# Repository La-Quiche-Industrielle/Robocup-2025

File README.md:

# Robocup-2025

## What is Robocup?
[Robocup Junior Soccer Open](https://junior.robocup.org/soccer/) is a league of the international robotic competition: [RoboCup](https://robocup.org).
For this competition, we need to create _two fully autonomous robots_ that play _soccer_ against other teams. We have to design, build and program the robots without external help. This is a really challenging problem because the robots need to be fully autonomous. They need to detect the ball and try to go towards it to hopefully push it towards the goal. A camera system is needed to try to detect the ball based on its color (it's an orange golf ball) and to detect the opponent's goal.

[Learn more about the competition](https://robocup-junior.github.io/soccer-rules/master/rules.html)

## The robots

The robots were built with individual components we found online, that we meshed together using communication protocols such as uart. The frames were 3d printed, and the cone was manufactured with CNC machining.

[More on the components we used](./components.md)

While we prepared for the competition, the robots could reliably place goals and were rather fast:

### What worked
The robots could reliably
- Find the ball
- Go towards the ball and place themselves in positions in which they could start moving towards the goal
- Shoot the ball / place a goal
- Avoid going out of bounds by staying a certain distance from walls
- Recenter when they couldn't see the ball. The robots could always see the ball from the center of the field (except if another robot was hiding it), so a centering function was enough to find the ball if it wasn't in the robot's field of visioin

### What failed
The robots broke in many ways during the national competition which meant we couldn't play for many of the matches:
- The wheels got disconnected from the motor's axies many times, which meant the whole robot became unable to play.
- Many of our N20 motors broke, which meant we didn't even have enough motors for both robots at the end of the competition
- An esp32 broke during the competition, and one of our replacement microcontrollers also failed when we opened the package.
- One of the batteries had a short circuit. Thankfully, the BMS (battery management system) protected the batteries from the short circuit. 

### How we'll fix these issues
- We created a simple 3d printed junction between the motors' axies and the wheels. This worked very well initially, but we hadn't taken the plastic's wear into account nearly enough. For next year, we'll only use metal components on important structural parts such as this.
- Last year, we chose N20 motors because of their low cost and good reviews. During the competitions, we often went above their torque limit, thus hurting the gears and breaking the motors. The N20 motors' torque is around 1kg.cm, and we realised that this wasn't nearly enough for what we wanted our robots to do. Next year, we'll invest in some better motors given sufficient funding, and hard code the torque limit into the program to slow the robots down before they could reach the torque limit and hurt the components.
- We bought many of our components on Aliexpress to reduce costs. Esp32s from aliexpress were within our price range, so we used these microcontrollers. For next year, we'll probably use better and faster microcontrollers such as a [teensy](https://www.sparkfun.com/development-boards/microcontrollers/teensy.html) and from better suppliers if we have the budget to do so.
- The battery had a short circuit because the wiring had become very difficult to work with. We had several dozens of wires going through the robot, and a positive and negative wire must have touched causing the short. This year, we tried designing a pcb, but it had a short circuit. Next year, we'll design a better pcb for the whole robot and try to find more data on pcb design before sending the design to a manufacturer.

### What we learned from our mistakes

___We can't expect the robots not to break:___
This year was a rather frustrating experience as we had worked very hard to create fast and functional robots only to see them fail miserably the day of the competition. We managed to have the robots place goals and avoid going out of bounds, and search for the ball if it couldn't see it and many other challenging actions only to see most components on the robots fail. We had spent hours programming the robots and making them move around on the field, and yet the numerous issues only arised the day of the competition. What we have learned from this is that we need to stress test our robots a lot more. We can no longer expect something to work only because it has worked in the past. Next year, we will push the robots to their limits. We will make them move until something breaks then rebuild that part with a lot more redundancy. We will also source better components given te ressources, and try to build redundancy into each and every part of the robot. We have learned that ___we can't expect that the robot won't break.___, but we need redundant systems to make sure that the system continues to work even if the primary system fails.

### License
This project is licensed under the Mozilla Public License 2.0 - see the [LICENSE](LICENSE) file for details.
## Our Website
Find out more about the team at laquicheindustrielle.com.

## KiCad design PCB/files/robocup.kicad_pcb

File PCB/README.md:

# Custom PCB Design

This is a 2-layer custom PCB designed in **KiCad 9** and manufactured via **JLCPCB**.

---

## About
  
the **PCB** was created using **KiCad 9**, with a focus on simplicity, and ease of assembly.

---

## Specs

-  **Layers**: 2
-  **EDA Tool**: KiCad 9
-  **Manufacturer**: JLCPCB
-  **Board Dimensions**: _[175mm x 175mm]_
-  **Ground pour for thermal management and EMI reduction.**

---

## 📁 Design Files

The following files are included in this repo:

- `*.kicad_pro` – KiCad 9 project file  
- `*.kicad_pcb` – PCB layout  
- `*.sch` – Schematic  
- `*.pdf` – Schematic2  

---

##  Manufacturing

These files were exported for and tested with **JLCPCB**.

- Designed using [KiCad](https://kicad.org/)
- Manufactured by [JLCPCB](https://jlcpcb.com)

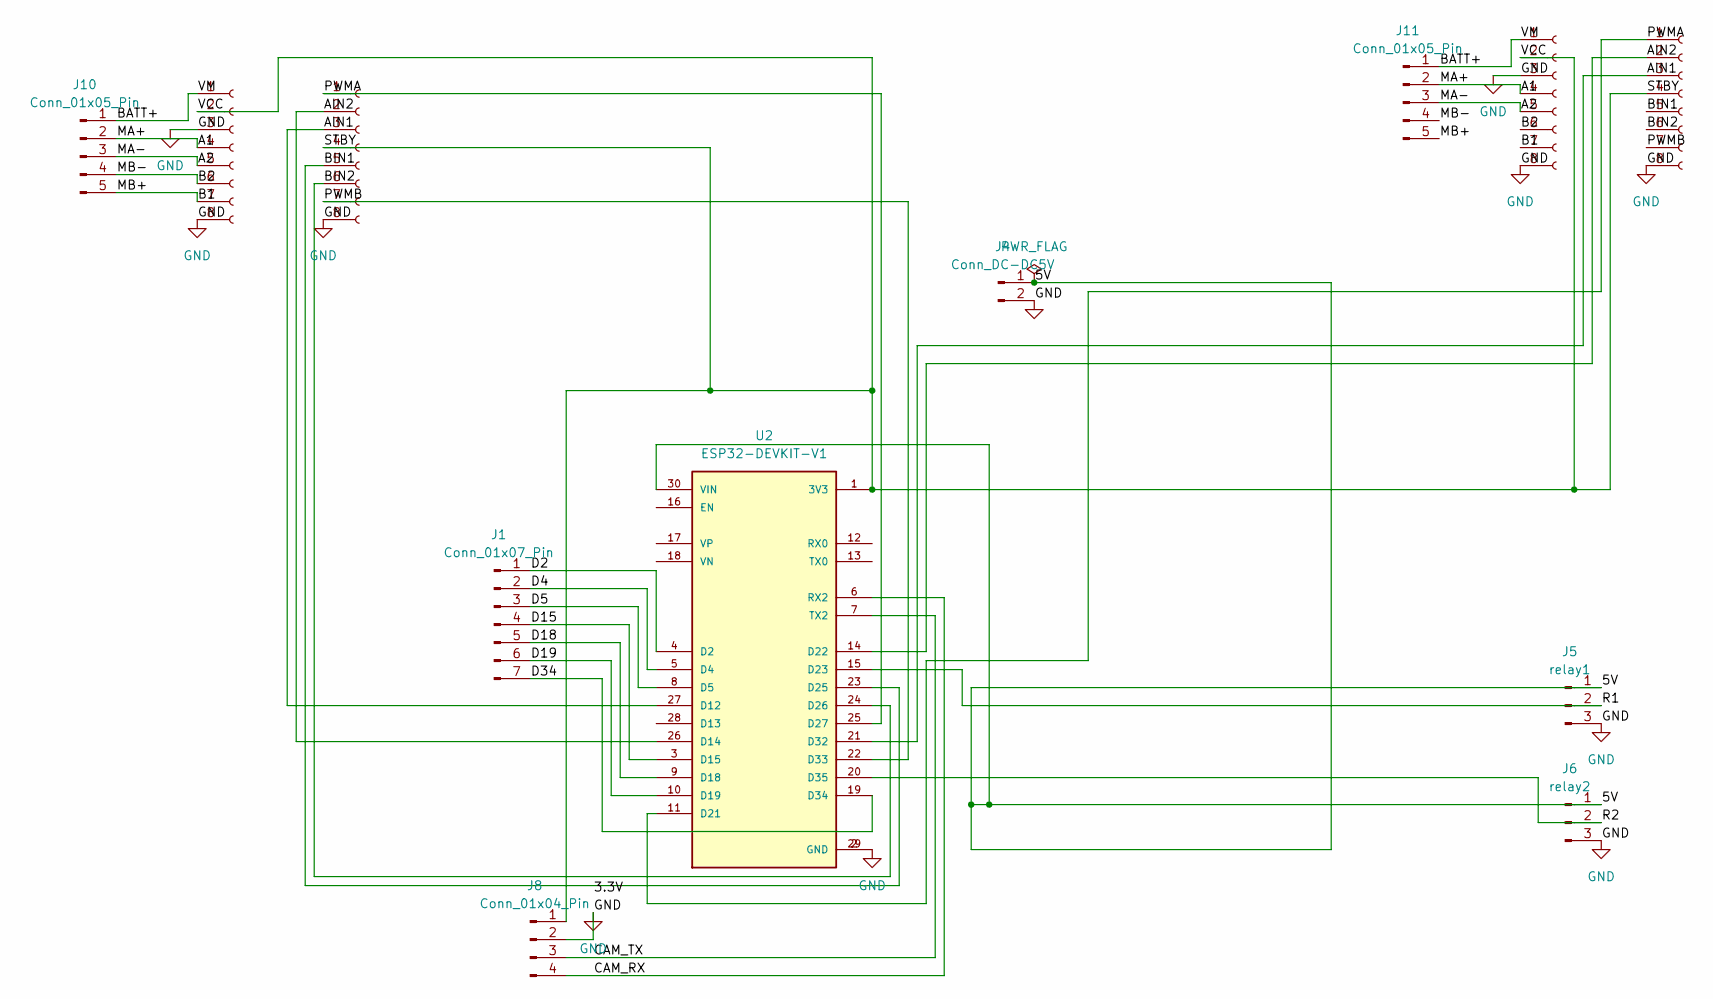
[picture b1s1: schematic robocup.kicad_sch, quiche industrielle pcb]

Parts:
J1: Conn_01x07_Pin; PinHeader_1x07_P2.54mm_Vertical
J2, J3, J7, J9: Conn_01x08_Socket; PinSocket_1x08_P2.54mm_Vertical
J4: Conn_DC-DC5V; PinHeader_1x02_P2.54mm_Vertical
J5: relay1; PinHeader_1x03_P2.54mm_Vertical
J6: relay2; PinHeader_1x03_P2.54mm_Vertical
J8: Conn_01x04_Pin; PinHeader_1x04_P2.54mm_Vertical
J10, J11: Conn_01x05_Pin; PinHeader_1x05_P2.54mm_Vertical
U2: ESP32-DEVKIT-V1; MODULE_ESP32_DEVKIT_V1; PARTREV N/A

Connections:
/5V: J4.1, J5.1, J6.1, U2.30 (VIN)
/A1: J2.4, J7.4, J10.2, J11.2
/A2: J2.5, J7.5, J10.3, J11.3
/AIN1: J3.3, J9.3, U2.21 (D32), U2.27 (D12)
/AIN2: J3.2, J9.2, U2.14 (D22), U2.26 (D14)
/B1: J2.7, J7.7, J10.5, J11.5
/B2: J2.6, J7.6, J10.4, J11.4
/BATT+: J2.1, J7.1, J10.1, J11.1
/BIN1: J3.5, J9.5, U2.23 (D25)
/BIN2: J3.6, J9.6, U2.24 (D26)
/CAM_RX: J8.4, U2.6 (RX2)
/CAM_TX: J8.3, U2.7 (TX2)
/D2: J1.1, U2.4 (D2)
/D4: J1.2, U2.5 (D4)
/D5: J1.3, U2.8 (D5)
/D15: J1.4, U2.3 (D15)
/D18: J1.5, U2.9 (D18)
/D19: J1.6, U2.10 (D19)
/D34: J1.7, U2.19 (D34)
/PWMA: J3.1, J9.1, U2.11 (D21), U2.25 (D27)
/PWMB: J3.7, J9.7, U2.22 (D33)
/R1: J5.2, U2.15 (D23)
/R2: J6.2, U2.20 (D35)
/STBY: J2.2, J3.4, J7.2, J8.1, J9.4, U2.1 (3V3)
GND: J2.3, J2.8, J3.8, J4.2, J5.3, J6.3, J7.3, J7.8, J8.2, J9.8, U2.2 (GND), U2.29 (GND)

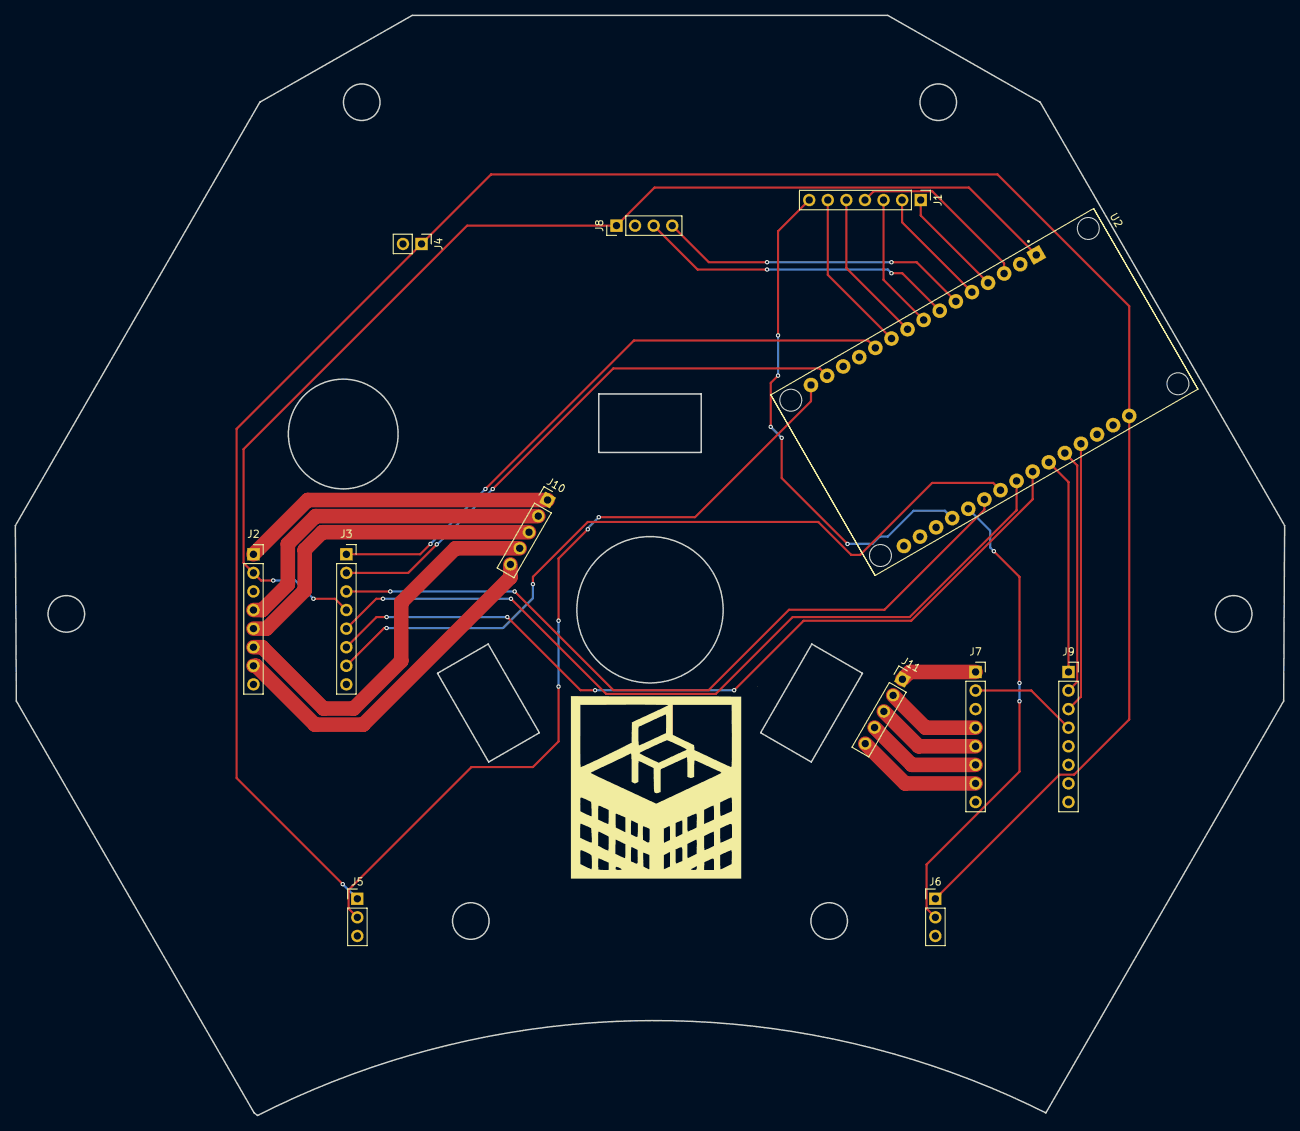
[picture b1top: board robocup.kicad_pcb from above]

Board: 2 copper layers, 173.5 x 150.4 mm, 12 parts (0 on the bottom side), 25 nets.

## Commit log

2025-07-25 adding media
2025-10-21 Create LISENCE
2025-10-21 LICENSE
2025-10-21 Update LICENSE
